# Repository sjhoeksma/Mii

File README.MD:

# Mii an Opensource Real Time, Timing solution
This solution can be used to create your own real time timing solution. It can be for example be used for mesuaring
the time needed to run a 10 meter sprint or do ski run.

We provide the hardware components, created with Eagle from CadSoft, emmbedded software written in arduino and a HTML5 app for Web & Mobile devices written with IONIC framework 1.3. For hardware components we provide the 3D models allowing you to print them your self.

## Components
1. MiiChrono and a MiiBeam make a start of finish line
2. MiiScoreboard can be used to show the time
3. MiiApp is the HMTL5 app
4. Mii3D are the 3D models for your printer in using openScad
5. Lib contains all libaries you need

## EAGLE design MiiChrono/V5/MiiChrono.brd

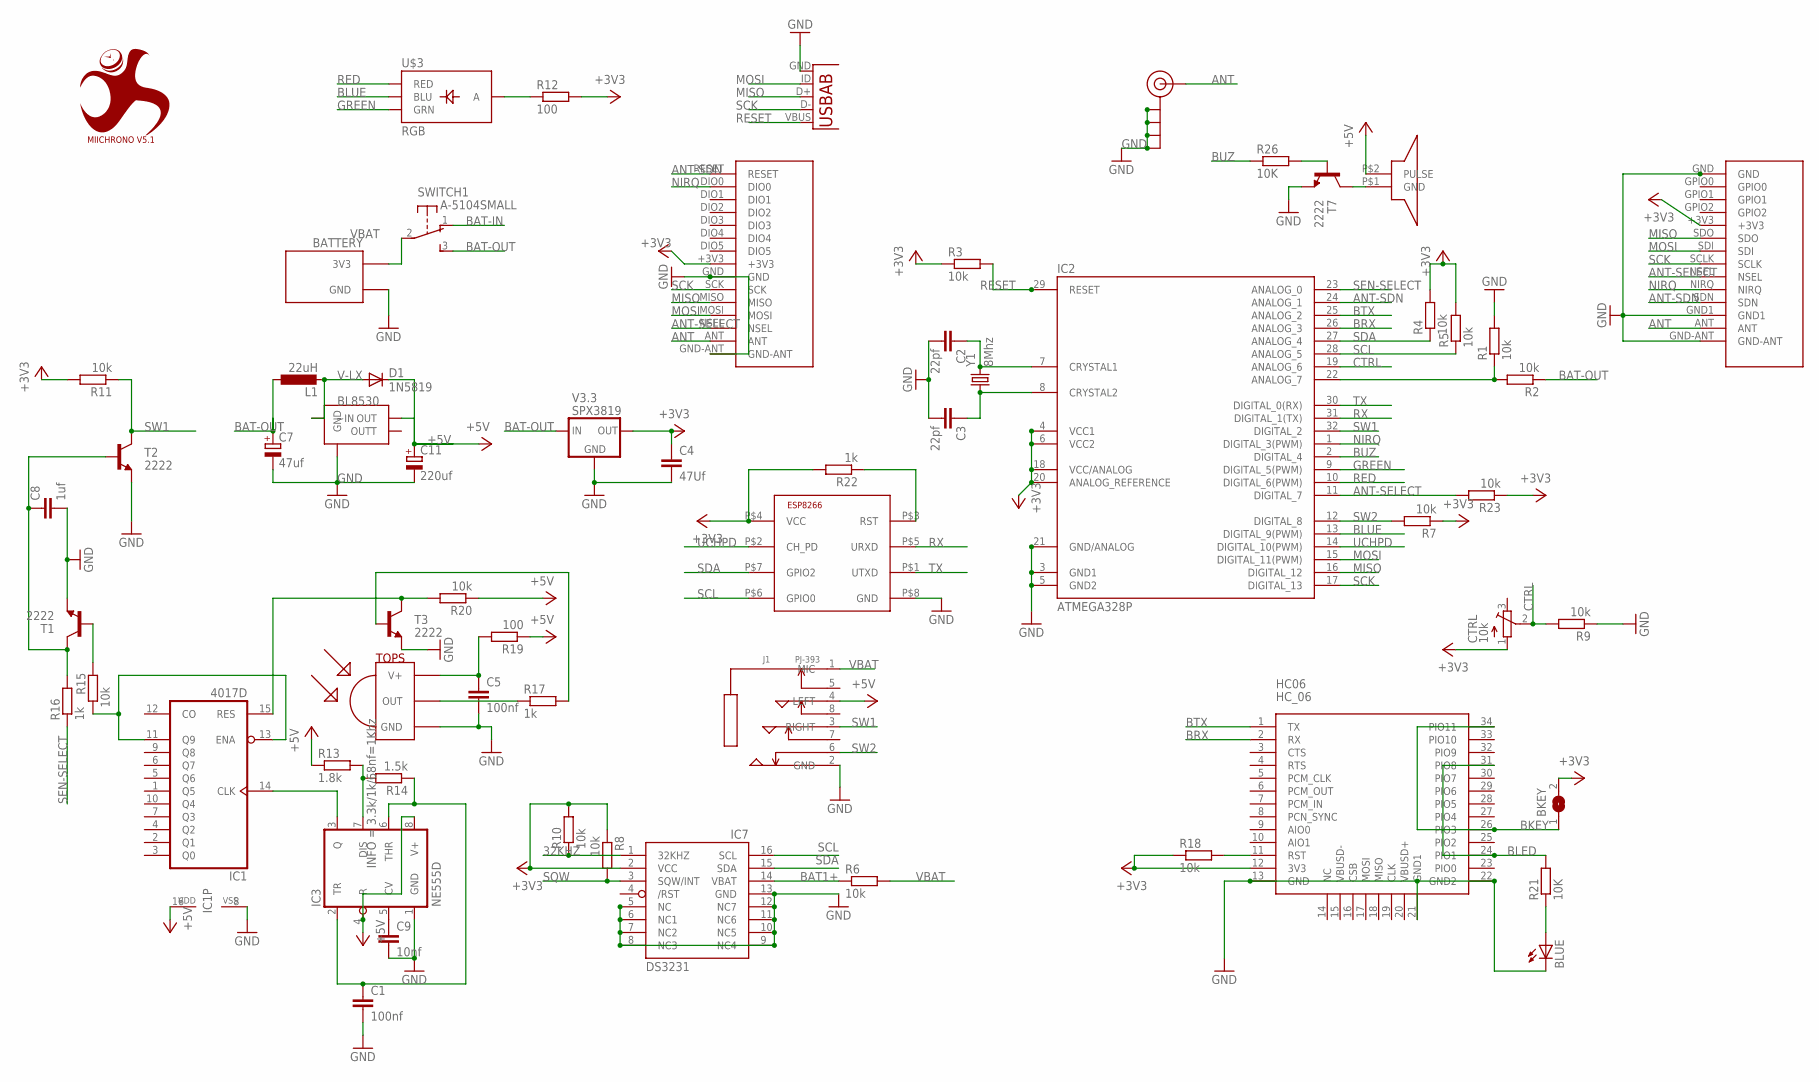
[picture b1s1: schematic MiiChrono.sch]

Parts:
BATTERY: GOPRO3BATTERY
BKEY: SOLDERJUMPER; SOLDERJUMPER_ARROW_NOPASTE
BL8530: BL8530; SOT89
BLUE: LEDCHIP-LED0805; CHIP-LED0805
BUZZER: BUZZER
C1, C5: 100nf; C0805
C2, C3: 22pf; C0805
C4: 47Uf; C0805
C7: 47uf; SMC_A
C8: 1uf; C0805
C9: 10nf; C0805
C11: 220uf; CT3528
CTRL: 10k; TC33X
D1: 1N5819; DO214AC
HC06: HC_06; BLUETOOTH_SMD
IC1: 4017D; SO16
IC2: ATMEGA328P; TQFP32-08
IC3: NE555D; SO08
IC7: DS3231/SO; SO16W
ISP1: USB-ABUSB_SIERK; USB_AB_MICRO_SJH
J1: PJ-393; AUDIO8P-SMD-3.5-14.5X6.1X4.0MM
J$1: SMA_EDGE; SMA-EDGE
L1: 22uH; L1812
R1, R2, R3, R4, R5, R6, R7, R8, R9, R10, R11, R15, R18, R20, R23: 10k; R0805
R12, R19: 100; R0805
R13: 1.8k; R0805
R14: 1.5k; R0805
R16, R17, R22: 1k; R0805
R21, R26: 10K; R0805
SWITCH: A-5104SMALL; A-5104-SMALL
T1, T2, T3, T7: 2222; SOT23
TOPS: TSOP4838; TSOP18XX
U$1: MIICHRONO V5.1; MIICHRONO
U$2: DRF1278F
U$3: RGB; LED-TRICOLOR-SMD
U$4: ESP8266-01; ESP-01
U$7: SI4432
V3.3: SPX3819; SOT23-5
Y1: 8Mhz; HC49UP

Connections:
32KHZ: IC7.1 (32KHZ), R10.1
+3V3: BKEY.2, C4.1, CTRL.1 (A), HC06.12 (3V3), IC2.4 (VCC1), IC2.6 (VCC2), IC2.18 (VCC/ANALOG), IC2.20 (ANALOG_REFERENCE), IC7.2 (VCC), R3.1, R4.2, R5.2, R7.1, R8.1, R10.2, R11.2, R12.2, R18.1, R22.2, R23.1, U$2.+3V3, U$4.P$4 (VCC), U$7.+3V3, V3.3.5 (OUT)
+5V: BL8530.2 (OUT), BUZZER.P$2 (PULSE), C11.+, D1.C, IC1.16 (VDD), IC3.4 (R), IC3.8 (V+), J1.4 (LEFT), R13.1, R19.1, R20.1
ANT: J$1.$P1 (SIGNAL), U$2.ANT, U$7.ANT
ANT-SDN: IC2.24 (ANALOG_1), U$2.RESET, U$7.SDN
ANT-SELECT: IC2.11 (DIGITAL_7), R23.2, U$2.NSEL, U$7.NSEL
BAT1+: IC7.14 (VBAT), R6.1
BAT-IN: SWITCH.1 (O)
BAT-OUT: C7.+, L1.1, R2.1, SWITCH.3 (S), V3.3.1 (IN), V3.3.3 (IN)
BKEY: BKEY.1, HC06.26 (PIO3), HC06.34 (PIO11)
BLED: HC06.24 (PIO1), HC06.31 (PIO8), R21.2
BLUE: IC2.13 (DIGITAL_9(PWM)), U$3.B (BLU)
BRX: HC06.2 (RX), IC2.26 (ANALOG_3)
BTX: HC06.1 (TX), IC2.25 (ANALOG_2)
BUZ: IC2.2 (DIGITAL_4), R26.1
CTRL: CTRL.2 (S), IC2.19 (ANALOG_6), R9.2
GND: BATTERY.GND, BL8530.1 (GND), BLUE.C, C1.2, C2.2, C3.2, C4.2, C5.2, C7.-, C8.2, C9.2, C11.-, HC06.13 (GND), HC06.21 (GND1), HC06.22 (GND2), IC1.8 (VSS), IC2.3 (GND1), IC2.5 (GND2), IC2.21 (GND/ANALOG), IC3.1 (GND), IC7.5 (NC), IC7.6 (NC1), IC7.7 (NC2), IC7.8 (NC3), IC7.9 (NC4), IC7.10 (NC5), IC7.11 (NC6), IC7.12 (NC7), IC7.13 (GND), ISP1.GND, J1.2 (GND), J$1.GND@0 (GND), J$1.GND@1 (GND), J$1.GND@2 (GND), J$1.GND@3 (GND), R1.2, R9.1, T1.2 (E), T2.2 (E), T3.2 (E), T7.2 (E), TOPS.GND, U$2.GND, U$2.GND-ANT, U$4.P$8 (GND), U$7.GND, U$7.GND1, U$7.GND-ANT, V3.3.2 (GND)
GREEN: IC2.9 (DIGITAL_5(PWM)), U$3.G (GRN)
MISO: IC2.16 (DIGITAL_12), ISP1.D+, U$2.MISO, U$7.SDO
MOSI: IC2.15 (DIGITAL_11(PWM)), ISP1.ID (USBID), U$2.MOSI, U$7.SDI
unnamed: R17.2, T3.1 (B)
unnamed: C9.1, IC3.5 (CV)
unnamed: HC06.11 (RST), R18.2
unnamed: C8.1, R16.2, T1.3 (C), T2.1 (B)
unnamed: IC1.11 (Q9), IC1.13 (ENA), R15.1
unnamed: R22.1, U$4.P$3 (RST)
unnamed: C3.1, IC2.8 (CRYSTAL2), Y1.1
unnamed: C2.1, IC2.7 (CRYSTAL1), Y1.2
unnamed: R15.2, T1.1 (B)
unnamed: R12.1, U$3.A
unnamed: C1.1, IC3.2 (TR), IC3.6 (THR), R14.1
unnamed: BLUE.A, R21.1
unnamed: IC1.14 (CLK), IC3.3 (Q)
unnamed: IC3.7 (DIS), R13.2, R14.2
unnamed: R17.1, TOPS.OUT
unnamed: C5.1, R19.2, TOPS.VCC (V+)
unnamed: IC1.15 (RES), R20.2, T3.3 (C)
unnamed: IC2.22 (ANALOG_7), R1.1, R2.2
unnamed: R26.2, T7.1 (B)
unnamed: BUZZER.P$1 (GND), T7.3 (C)
NIRQ: IC2.1 (DIGITAL_3(PWM)), U$2.DIO0, U$7.NIRQ
RED: IC2.10 (DIGITAL_6(PWM)), U$3.R (RED)
RESET: IC2.29 (RESET), ISP1.VBUS, R3.2
RX: IC2.31 (DIGITAL_1(TX)), U$4.P$5 (URXD)
SCK: IC2.17 (DIGITAL_13), ISP1.D-, U$2.SCK, U$7.SCLK
SCL: IC2.28 (ANALOG_5), IC7.16 (SCL), R5.1, U$4.P$6 (GPIO0)
SDA: IC2.27 (ANALOG_4), IC7.15 (SDA), R4.1, U$4.P$7 (GPIO2)
SEN-SELECT: IC2.23 (ANALOG_0), R16.1
SQW: IC7.3 (SQW/INT), R8.2
SW1: IC2.32 (DIGITAL_2), J1.3 (RIGHT), R11.1, T2.3 (C)
SW2: IC2.12 (DIGITAL_8), J1.6, R7.2
TX: IC2.30 (DIGITAL_0(RX)), U$4.P$1 (UTXD)
UCHPD: IC2.14 (DIGITAL_10(PWM)), U$4.P$2 (CH_PD)
V-LX: BL8530.3 (~IN), D1.A, L1.2
VBAT: BATTERY.3V3, J1.1 (MIC), R6.2, SWITCH.2

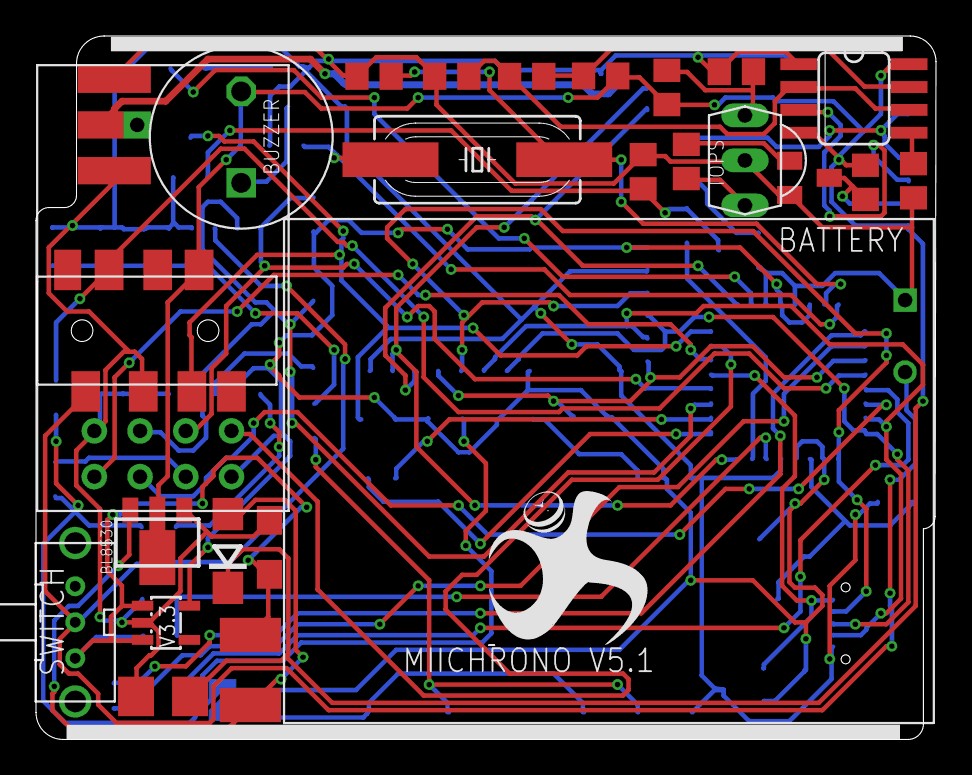
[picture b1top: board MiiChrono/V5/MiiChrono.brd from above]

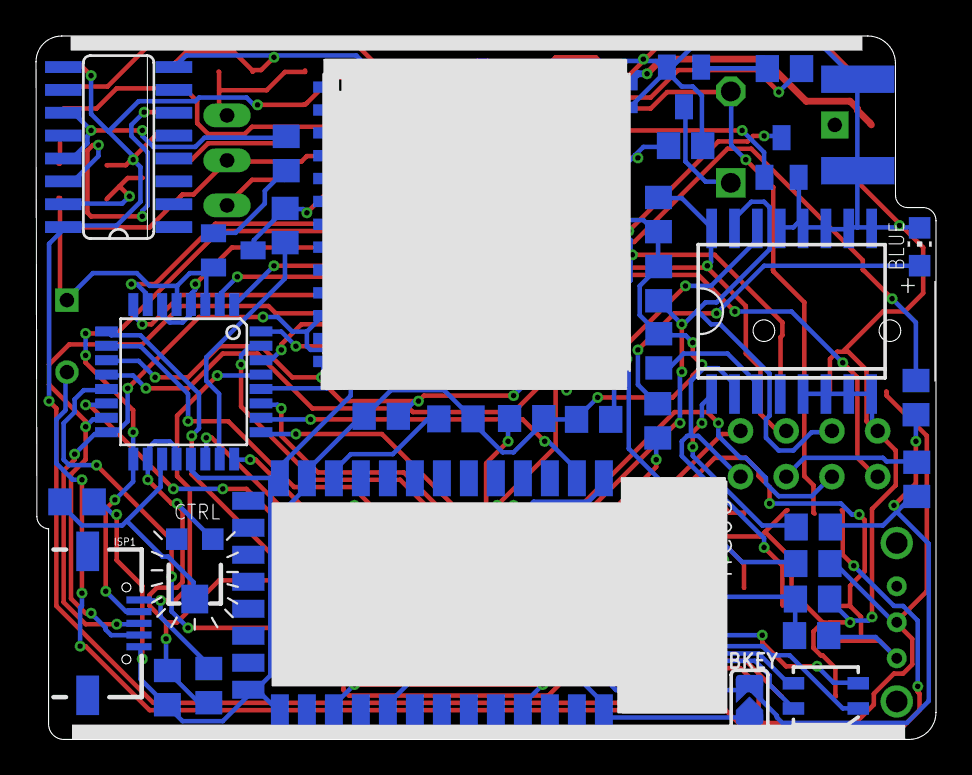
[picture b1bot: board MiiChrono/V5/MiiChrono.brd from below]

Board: 2 copper layers, 50.0 x 39.1 mm, 62 parts (35 on the bottom side), 54 nets.

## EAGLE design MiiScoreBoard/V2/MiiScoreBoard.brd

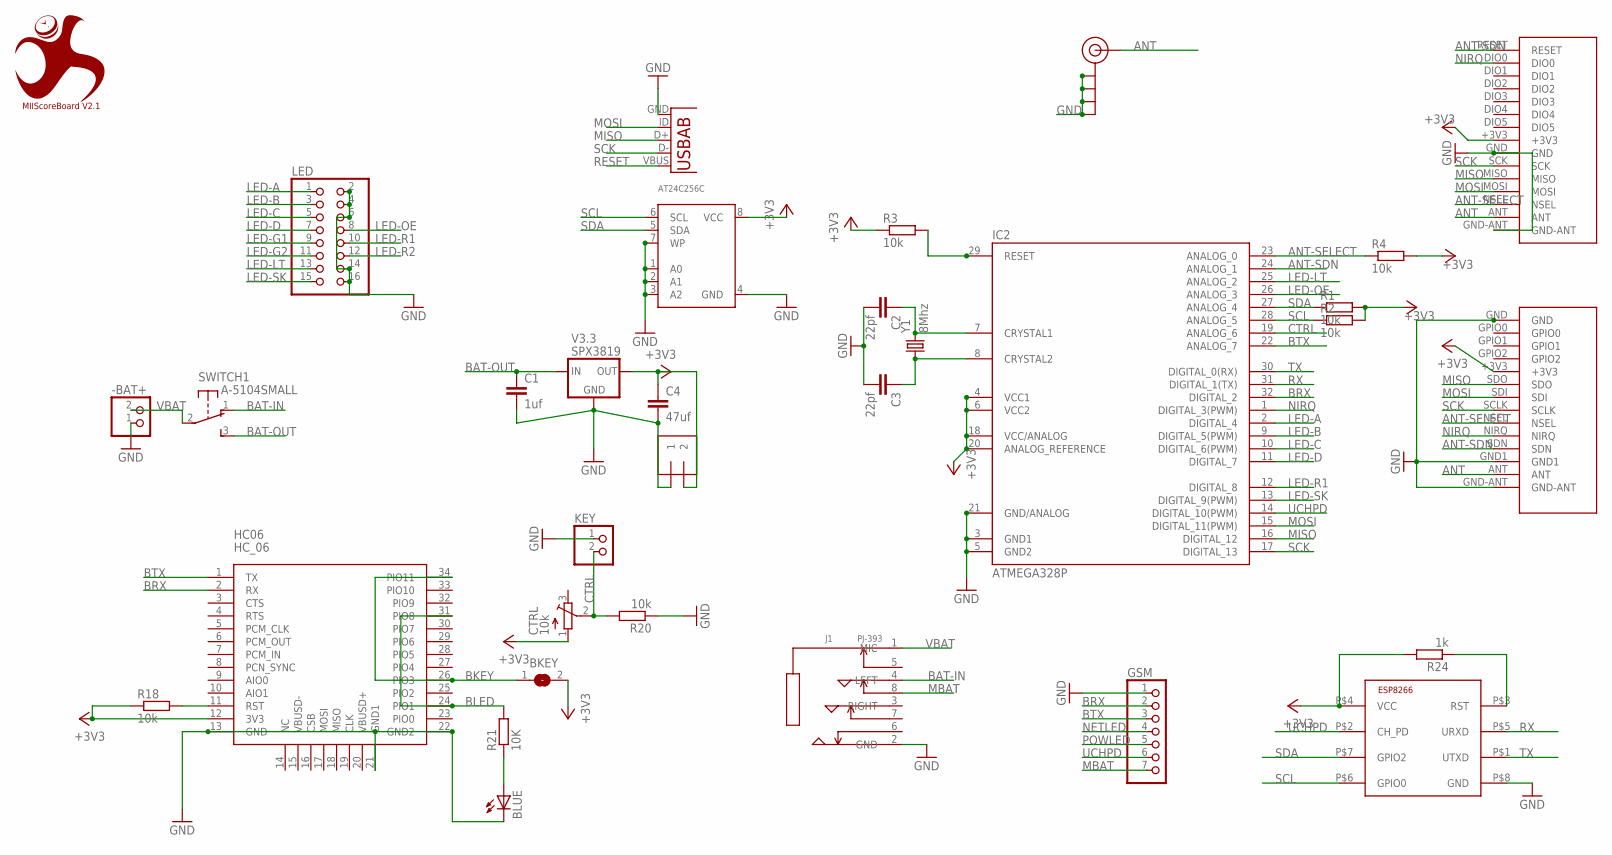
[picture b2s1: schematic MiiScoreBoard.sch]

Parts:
-BAT+: JST_2PIN-THM; JST-PH-2-THM
-LED+: -BAT+; 1X2-3.5MM
AT24C256C: EEPROM_I2C_SOIC8_GENERIC; SOIC8_150MIL
BKEY: SOLDERJUMPER; SOLDERJUMPER_ARROW_NOPASTE
BLUE: LEDCHIP-LED0805; CHIP-LED0805
C1: 1uf; C0805
C2, C3: 22pf; C0805
C4: 47uf; C0805
CTRL: 10k; TC33X
GSM: PINHD-1X07_2.54; 1X07
HC06: HC_06; BLUETOOTH_SMD
IC2: ATMEGA328P; TQFP32-08
ISP1: USB-ABUSB_SIERK; USB_AB_MICRO_SJH
J1: PJ-393; AUDIO8P-SMD-3.5-14.5X6.1X4.0MM
J$1: SMA_EDGE; SMA-EDGE
KEY: PINHD-1X02_2.54-90°; 1X02/90
LED: PINHD-2X08_2.54; 2X08
R1, R2, R3, R4, R18, R20: 10k; R0805
R21: 10K; R0805
R24: 1k; R0805
SWITCH: A-5104SMALL; A-5104-SMALL
U$1: MIIScoreBoard V2.1; MIICHRONO
U$2: DRF1278F
U$6: ESP8266-01; ESP-01
U$7: SI4432
V3.3: SPX3819; SOT23-5
Y1: 8Mhz; HC49UP

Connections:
+3V3: -LED+.2, AT24C256C.8 (VCC), BKEY.2, C4.1, CTRL.1 (A), HC06.12 (3V3), IC2.4 (VCC1), IC2.6 (VCC2), IC2.18 (VCC/ANALOG), IC2.20 (ANALOG_REFERENCE), R1.2, R2.2, R3.1, R4.2, R18.1, R24.2, U$2.+3V3, U$6.P$4 (VCC), U$7.+3V3, V3.3.5 (OUT)
ANT: J$1.$P1 (SIGNAL), U$2.ANT, U$7.ANT
ANT-SDN: IC2.24 (ANALOG_1), U$2.RESET, U$7.SDN
ANT-SELECT: IC2.23 (ANALOG_0), R4.1, U$2.NSEL, U$7.NSEL
BAT-IN: J1.4 (LEFT), SWITCH.1 (O)
BAT-OUT: C1.1, SWITCH.3 (S), V3.3.1 (IN), V3.3.3 (IN)
BKEY: BKEY.1, HC06.26 (PIO3), HC06.34 (PIO11)
BLED: HC06.24 (PIO1), HC06.31 (PIO8), R21.2
BRX: GSM.2, HC06.2 (RX), IC2.32 (DIGITAL_2)
BTX: GSM.3, HC06.1 (TX), IC2.22 (ANALOG_7)
CTRL: CTRL.2 (S), IC2.19 (ANALOG_6), KEY.2, R20.2
GND: -BAT+.1 (2), -LED+.1, AT24C256C.1 (A0), AT24C256C.2 (A1), AT24C256C.3 (A2), AT24C256C.4 (GND), AT24C256C.7 (WP), BLUE.C, C1.2, C2.2, C3.2, C4.2, GSM.1, HC06.13 (GND), HC06.21 (GND1), HC06.22 (GND2), IC2.3 (GND1), IC2.5 (GND2), IC2.21 (GND/ANALOG), ISP1.GND, J1.2 (GND), J$1.GND@0 (GND), J$1.GND@1 (GND), J$1.GND@2 (GND), J$1.GND@3 (GND), KEY.1, LED.2, LED.4, LED.6, LED.14, LED.16, R20.1, U$2.GND, U$2.GND-ANT, U$6.P$8 (GND), U$7.GND, U$7.GND1, U$7.GND-ANT, V3.3.2 (GND)
LED-A: IC2.2 (DIGITAL_4), LED.1
LED-B: IC2.9 (DIGITAL_5(PWM)), LED.3
LED-C: IC2.10 (DIGITAL_6(PWM)), LED.5
LED-D: IC2.11 (DIGITAL_7), LED.7
LED-G1: LED.9
LED-G2: LED.11
LED-LT: IC2.25 (ANALOG_2), LED.13
LED-OE: IC2.26 (ANALOG_3), LED.8
LED-R1: IC2.12 (DIGITAL_8), LED.10
LED-R2: LED.12
LED-SK: IC2.13 (DIGITAL_9(PWM)), LED.15
MBAT: GSM.7, J1.8
MISO: IC2.16 (DIGITAL_12), ISP1.D+, U$2.MISO, U$7.SDO
MOSI: IC2.15 (DIGITAL_11(PWM)), ISP1.ID (USBID), U$2.MOSI, U$7.SDI
unnamed: HC06.11 (RST), R18.2
unnamed: C3.1, IC2.8 (CRYSTAL2), Y1.1
unnamed: C2.1, IC2.7 (CRYSTAL1), Y1.2
unnamed: R24.1, U$6.P$3 (RST)
unnamed: BLUE.A, R21.1
NETLED: GSM.4
NIRQ: IC2.1 (DIGITAL_3(PWM)), U$2.DIO0, U$7.NIRQ
POWLED: GSM.5
RESET: IC2.29 (RESET), ISP1.VBUS, R3.2
RX: IC2.31 (DIGITAL_1(TX)), U$6.P$5 (URXD)
SCK: IC2.17 (DIGITAL_13), ISP1.D-, U$2.SCK, U$7.SCLK
SCL: AT24C256C.6 (SCL), IC2.28 (ANALOG_5), R2.1, U$6.P$6 (GPIO0)
SDA: AT24C256C.5 (SDA), IC2.27 (ANALOG_4), R1.1, U$6.P$7 (GPIO2)
TX: IC2.30 (DIGITAL_0(RX)), U$6.P$1 (UTXD)
UCHPD: GSM.6, IC2.14 (DIGITAL_10(PWM)), U$6.P$2 (CH_PD)
VBAT: -BAT+.2 (1), J1.1 (MIC), SWITCH.2

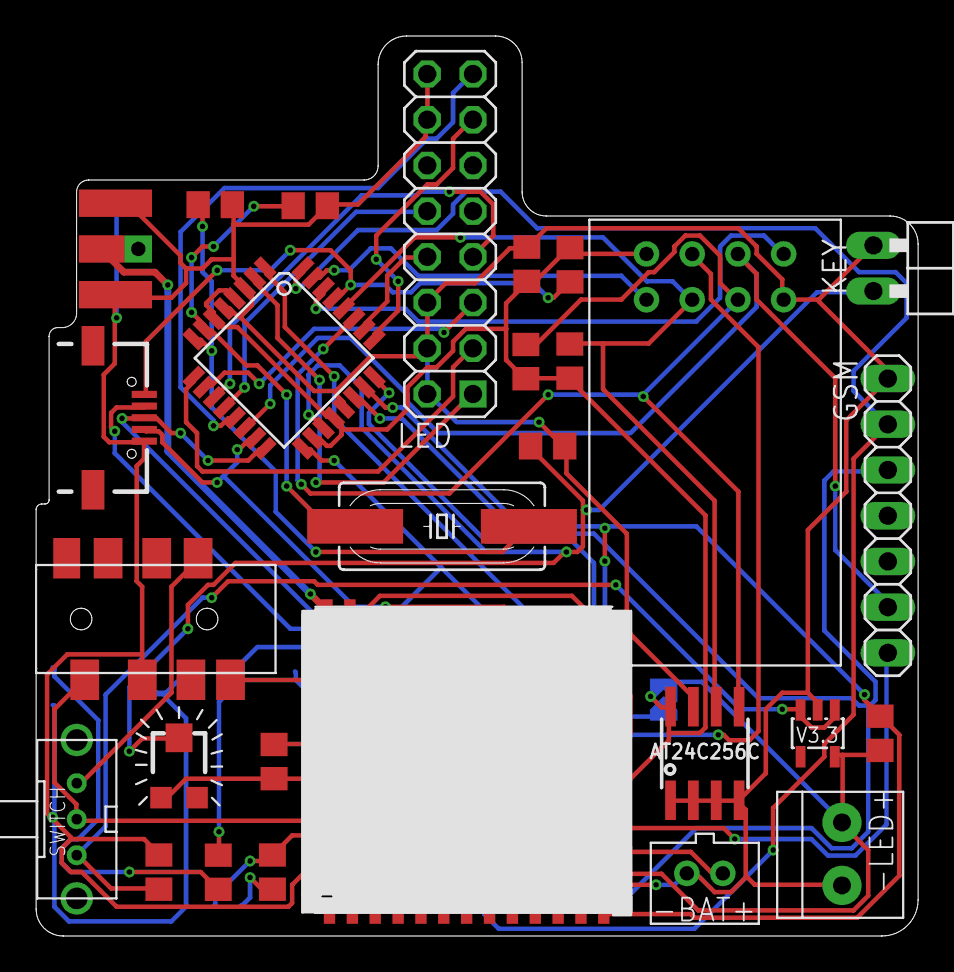
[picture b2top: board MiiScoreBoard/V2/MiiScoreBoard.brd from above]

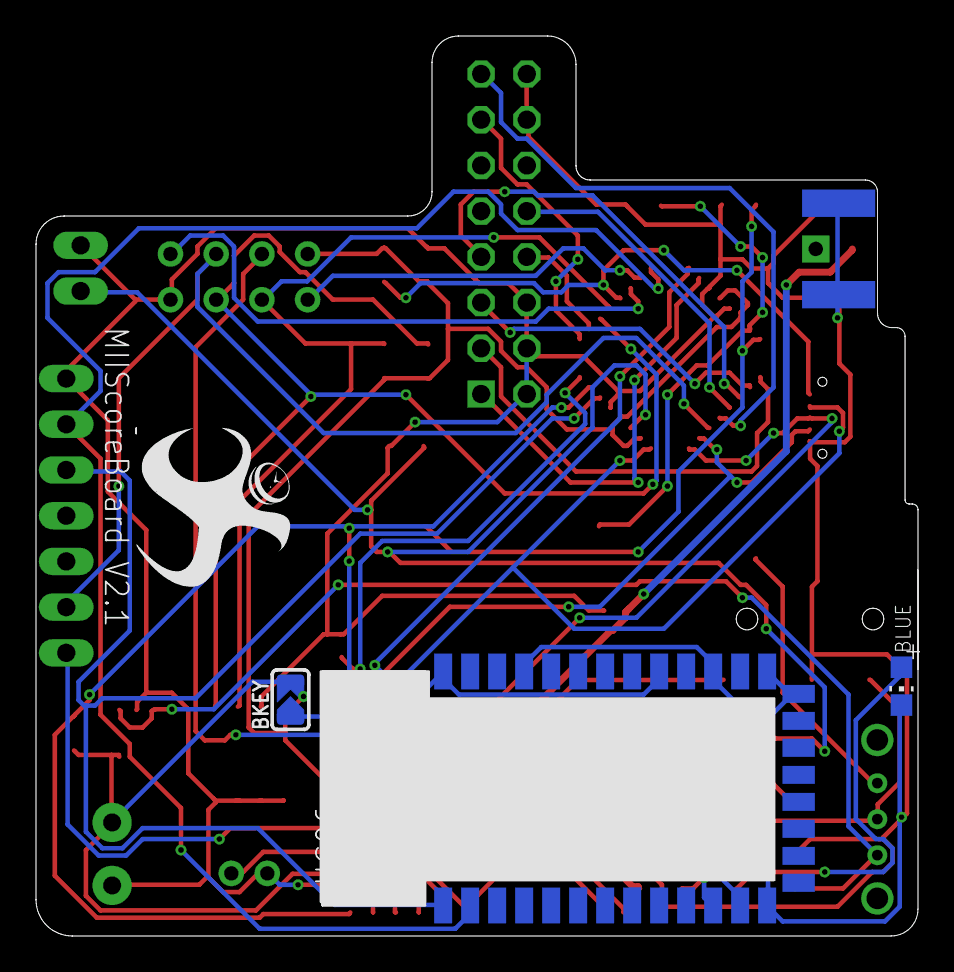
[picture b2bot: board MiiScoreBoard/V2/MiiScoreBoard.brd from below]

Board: 2 copper layers, 49.0 x 50.0 mm, 33 parts (4 on the bottom side), 37 nets.

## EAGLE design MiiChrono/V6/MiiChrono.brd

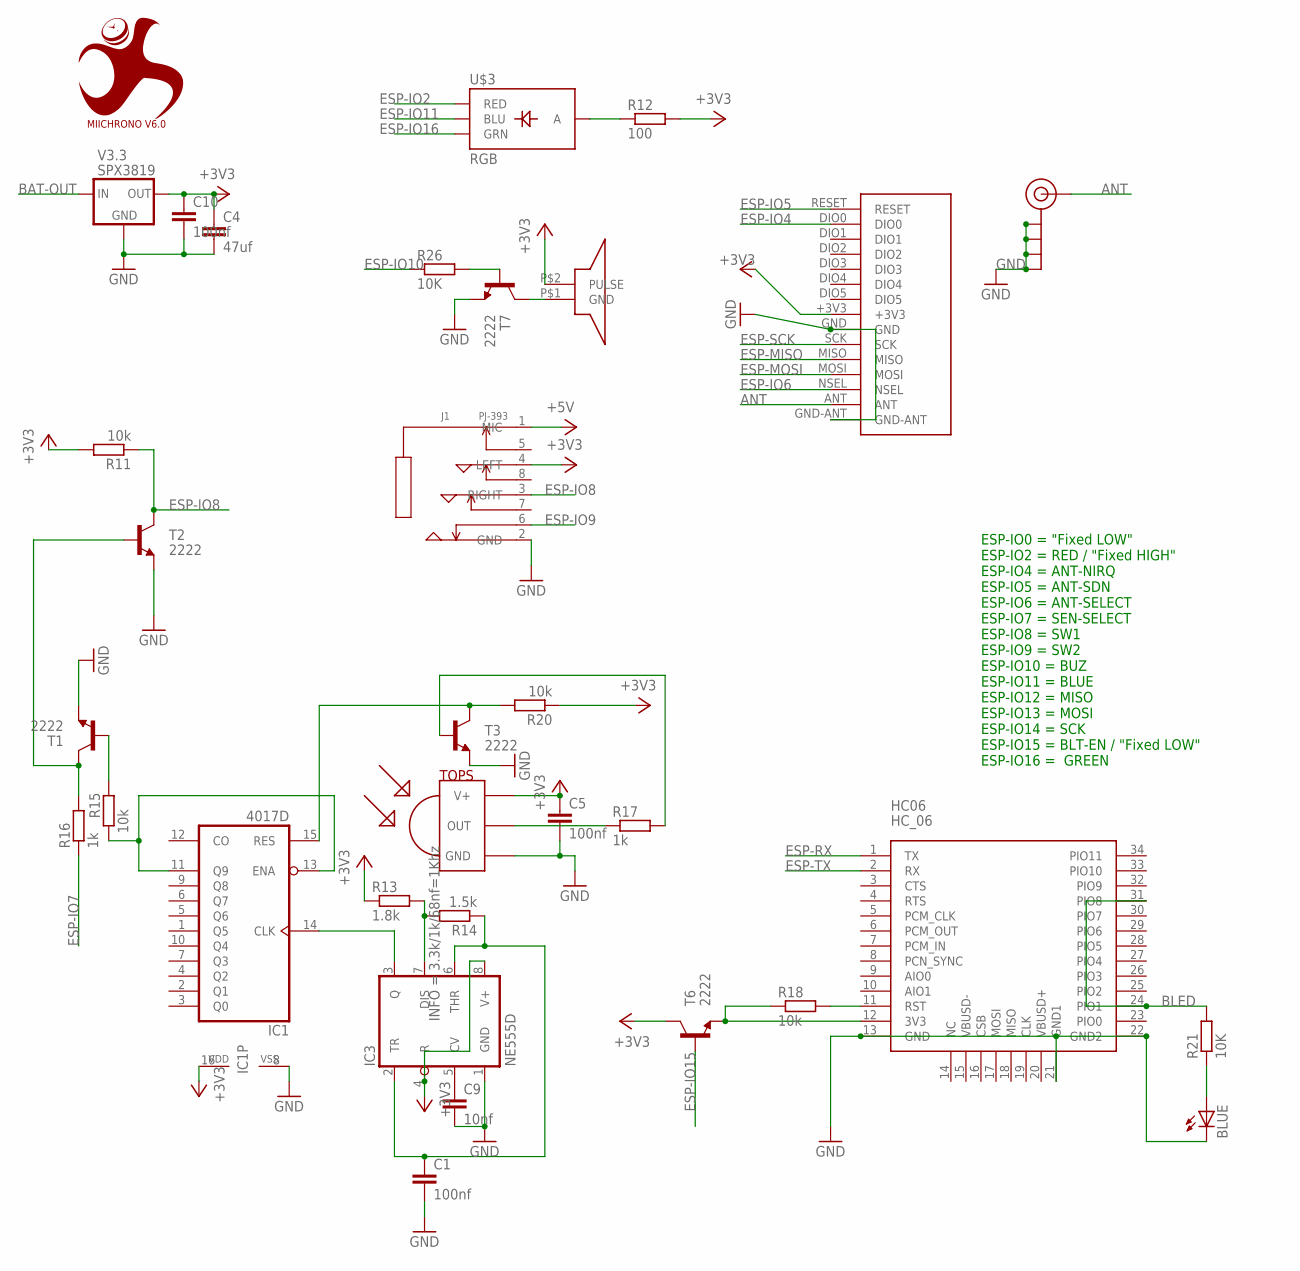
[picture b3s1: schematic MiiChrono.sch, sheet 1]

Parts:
BLUE: LEDCHIP-LED0805; CHIP-LED0805
BUZZER: BUZZER
C1, C5, C10: 100nf; C0805
C4: 47uf; C0805
C9: 10nf; C0805
HC06: HC_06; BLUETOOTH_SMD
IC1: 4017D; SO16
IC3: NE555D; SO08
J1: PJ-393; AUDIO8P-SMD-3.5-14.5X6.1X4.0MM
J$1: SMA_EDGE; SMA-EDGE
R11, R15, R18, R20: 10k; R0805
R12: 100; R0805
R13: 1.8k; R0805
R14: 1.5k; R0805
R16, R17: 1k; R0805
R21, R26: 10K; R0805
T1, T2, T3, T6, T7: 2222; SOT23
TOPS: TSOP4838; TSOP18XX
U$1: MIICHRONO V6.0; MIICHRONO
U$2: DRF1278F
U$3: RGB; LED-TRICOLOR-SMD
V3.3: SPX3819; SOT23-5

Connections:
+3V3: BUZZER.P$2 (PULSE), C4.1, C5.1, C10.1, IC1.16 (VDD), IC3.4 (R), IC3.8 (V+), J1.4 (LEFT), R11.2, R12.2, R13.1, R20.1, T6.3 (C), TOPS.VCC (V+), U$2.+3V3, V3.3.5 (OUT)
+5V: J1.1 (MIC); also elsewhere on the board
ANT: J$1.$P1 (SIGNAL), U$2.ANT
BAT-OUT: V3.3.1 (IN), V3.3.3 (IN); also elsewhere on the board
BLED: HC06.24 (PIO1), HC06.31 (PIO8), R21.2
ESP-IO2: U$3.R (RED); also elsewhere on the board
ESP-IO4: U$2.DIO0; also elsewhere on the board
ESP-IO5: U$2.RESET; also elsewhere on the board
ESP-IO6: U$2.NSEL; also elsewhere on the board
ESP-IO7: R16.1; also elsewhere on the board
ESP-IO8: J1.3 (RIGHT), R11.1, T2.3 (C); also elsewhere on the board
ESP-IO9: J1.6; also elsewhere on the board
ESP-IO10: R26.1; also elsewhere on the board
ESP-IO11: U$3.B (BLU); also elsewhere on the board
ESP-IO15: T6.1 (B); also elsewhere on the board
ESP-IO16: U$3.G (GRN); also elsewhere on the board
ESP-MISO: U$2.MISO; also elsewhere on the board
ESP-MOSI: U$2.MOSI; also elsewhere on the board
ESP-RX: HC06.1 (TX); also elsewhere on the board
ESP-SCK: U$2.SCK; also elsewhere on the board
ESP-TX: HC06.2 (RX); also elsewhere on the board
GND: BLUE.C, C1.2, C4.2, C5.2, C9.2, C10.2, HC06.13 (GND), HC06.21 (GND1), HC06.22 (GND2), IC1.8 (VSS), IC3.1 (GND), J1.2 (GND), J$1.GND@0 (GND), J$1.GND@1 (GND), J$1.GND@2 (GND), J$1.GND@3 (GND), T1.2 (E), T2.2 (E), T3.2 (E), T7.2 (E), TOPS.GND, U$2.GND, U$2.GND-ANT, V3.3.2 (GND); also elsewhere on the board
unnamed: R17.2, T3.1 (B)
unnamed: C9.1, IC3.5 (CV)
unnamed: R16.2, T1.3 (C), T2.1 (B)
unnamed: IC1.11 (Q9), IC1.13 (ENA), R15.1
unnamed: HC06.12 (3V3), R18.1, T6.2 (E)
unnamed: R15.2, T1.1 (B)
unnamed: R12.1, U$3.A
unnamed: C1.1, IC3.2 (TR), IC3.6 (THR), R14.1
unnamed: HC06.11 (RST), R18.2
unnamed: IC1.14 (CLK), IC3.3 (Q)
unnamed: IC3.7 (DIS), R13.2, R14.2
unnamed: R17.1, TOPS.OUT
unnamed: BLUE.A, R21.1
unnamed: IC1.15 (RES), R20.2, T3.3 (C)
unnamed: R26.2, T7.1 (B)
unnamed: BUZZER.P$1 (GND), T7.3 (C)

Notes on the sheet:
ESP-IO0 = "Fixed LOW" ESP-IO2 = RED / "Fixed HIGH" ESP-IO4 = ANT-NIRQ ESP-IO5 = ANT-SDN ESP-IO6 = ANT-SELECT ESP-IO7 = SEN-SELECT ESP-IO8 = SW1 ESP-IO9 = SW2 ESP-IO10 = BUZ ESP-IO11 = BLUE ESP-IO12 = MISO ESP-IO13 = MOSI ESP-IO14 = SCK ESP-IO15 = BLT-EN / "Fixed LOW" ESP-IO16 = GREEN

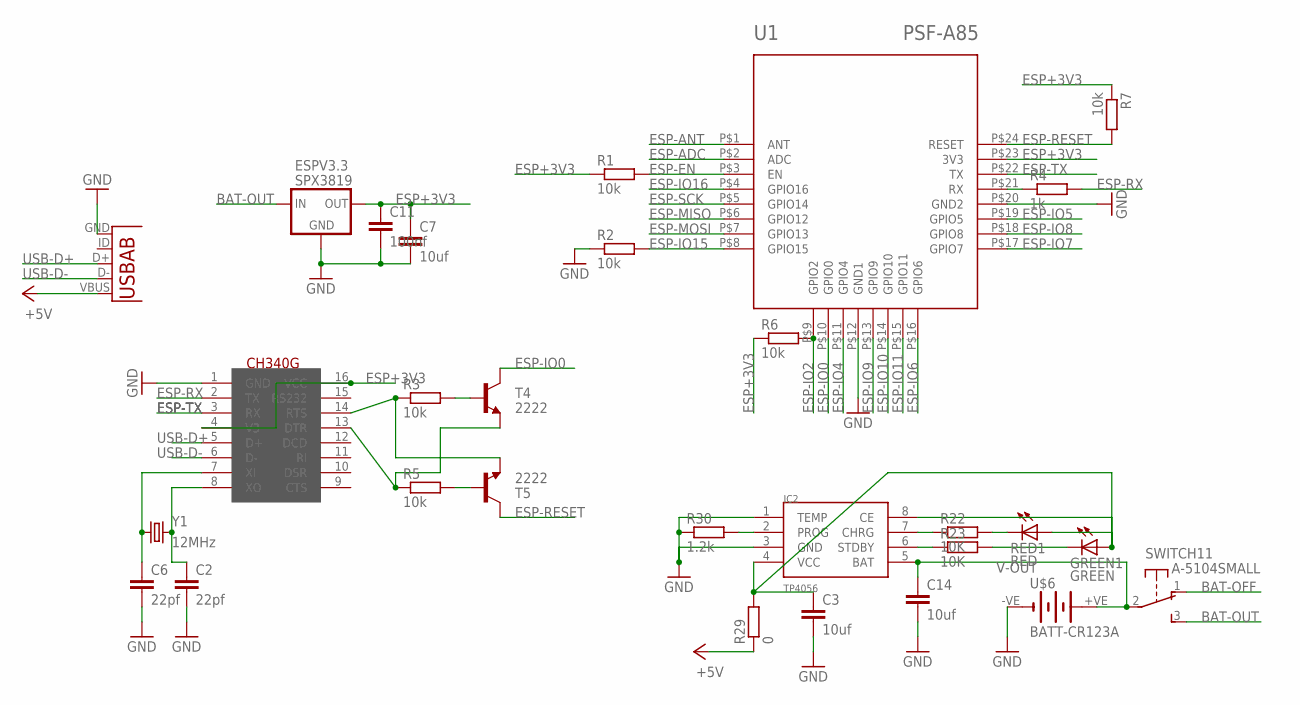
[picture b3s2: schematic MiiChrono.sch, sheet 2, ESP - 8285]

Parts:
C2, C6: 22pf; C0805
C3, C7, C14: 10uf; C0805
C11: 100nf; C0805
ESPV3.3: SPX3819; SOT23-5
GREEN1: GREEN; CHIP-LED0805
IC2: TP4056; SOP-8
ISP2: USB-ABUSB_SIERK; USB_AB_MICRO_SJH
R1, R2, R3, R5, R6, R7: 10k; R0805
R4: 1k; R0805
R22, R23: 10K; R0805
R29: 0; R0805
R30: 1.2k; R0805
RED1: RED; CHIP-LED0805
SWITCH1: A-5104SMALL; A-5104-SMALL
T4, T5: 2222; SOT23
U1: PSF-A85
U$5: CH340G; SOIC16
U$6: BATT-CR123A; KEYSTONE-2/3A
Y1: 12MHz; CRYSTAL-SMD-5X3

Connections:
+5V: ISP2.VBUS, R29.1; also elsewhere on the board
BAT-OFF: SWITCH1.1 (O)
BAT-OUT: ESPV3.3.1 (IN), ESPV3.3.3 (IN), SWITCH1.3 (S); also elsewhere on the board
ESP+3V3: C7.1, C11.1, ESPV3.3.5 (OUT), R1.1, R6.1, R7.1, U1.P$23 (3V3), U$5.4 (V3), U$5.16 (VCC)
ESP-ADC: U1.P$2 (ADC)
ESP-ANT: U1.P$1 (ANT)
ESP-EN: R1.2, U1.P$3 (EN)
ESP-IO0: T4.3 (C), U1.P$10 (GPIO0)
ESP-IO2: R6.2, U1.P$9 (GPIO2); also elsewhere on the board
ESP-IO4: U1.P$11 (GPIO4); also elsewhere on the board
ESP-IO5: U1.P$19 (GPIO5); also elsewhere on the board
ESP-IO6: U1.P$16 (GPIO6); also elsewhere on the board
ESP-IO7: U1.P$17 (GPIO7); also elsewhere on the board
ESP-IO8: U1.P$18 (GPIO8); also elsewhere on the board
ESP-IO9: U1.P$13 (GPIO9); also elsewhere on the board
ESP-IO10: U1.P$14 (GPIO10); also elsewhere on the board
ESP-IO11: U1.P$15 (GPIO11); also elsewhere on the board
ESP-IO15: R2.2, U1.P$8 (GPIO15); also elsewhere on the board
ESP-IO16: U1.P$4 (GPIO16); also elsewhere on the board
ESP-MISO: U1.P$6 (GPIO12); also elsewhere on the board
ESP-MOSI: U1.P$7 (GPIO13); also elsewhere on the board
ESP-RESET: R7.2, T5.3 (C), U1.P$24 (RESET)
ESP-RX: R4.2, U$5.2 (TX); also elsewhere on the board
ESP-SCK: U1.P$5 (GPIO14); also elsewhere on the board
ESP-TX: U1.P$22 (TX), U$5.3 (RX); also elsewhere on the board
GND: C2.2, C3.2, C6.2, C7.2, C11.2, C14.2, ESPV3.3.2 (GND), IC2.1 (TEMP), IC2.3 (GND), ISP2.GND, R2.1, R30.1, U1.P$12 (GND1), U1.P$20 (GND2), U$5.1 (GND), U$6.-VE (-); also elsewhere on the board
unnamed: C6.1, U$5.7 (XI), Y1.1
unnamed: C2.1, U$5.8 (XO), Y1.3 (2)
unnamed: R3.1, T5.2 (E), U$5.14 (RTS)
unnamed: R5.1, T4.2 (E), U$5.13 (DTR)
unnamed: R5.2, T5.1 (B)
unnamed: R3.2, T4.1 (B)
unnamed: R4.1, U1.P$21 (RX)
unnamed: GREEN1.C, R23.2
unnamed: R22.2, RED1.C
unnamed: IC2.7 (CHRG), R22.1
unnamed: IC2.6 (STDBY), R23.1
unnamed: IC2.2 (PROG), R30.2
USB-D+: ISP2.D+, U$5.5 (D+)
USB-D-: ISP2.D-, U$5.6 (D-)
V-IN: C3.1, GREEN1.A, IC2.4 (VCC), IC2.8 (CE), R29.2, RED1.A
V-OUT: C14.1, IC2.5 (BAT), SWITCH1.2, U$6.+VE (+)

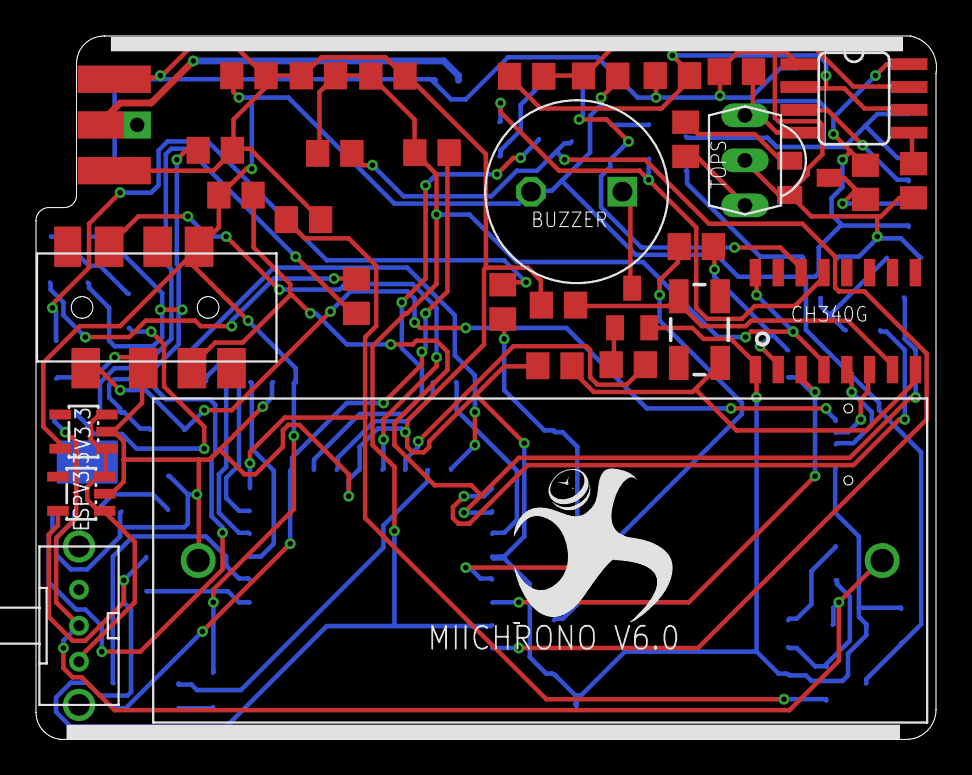
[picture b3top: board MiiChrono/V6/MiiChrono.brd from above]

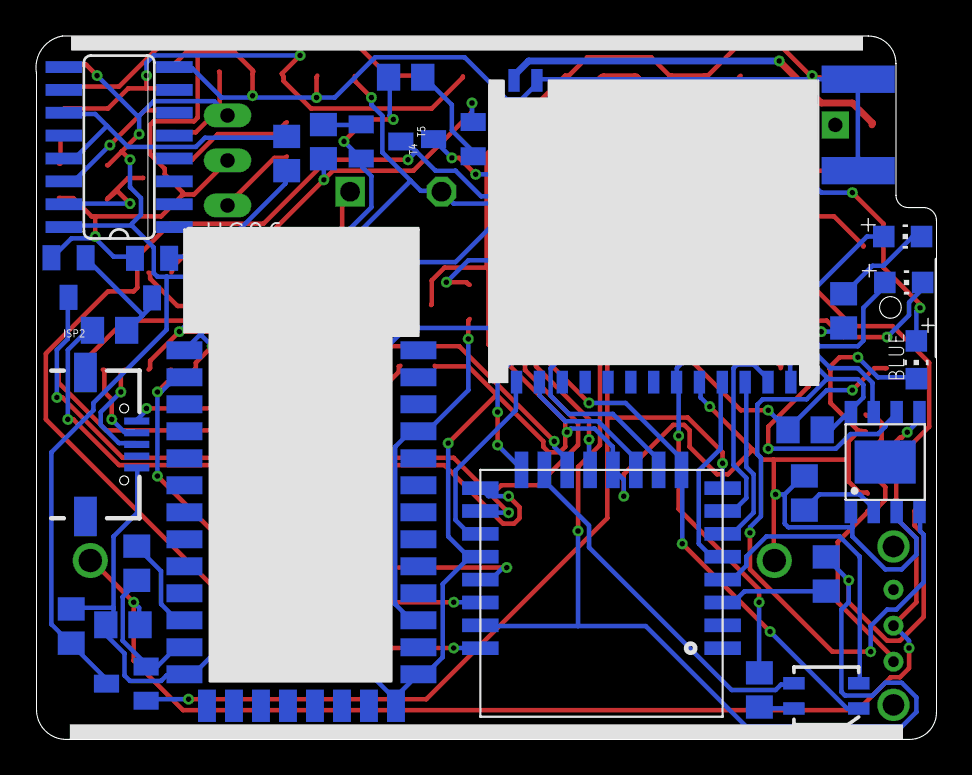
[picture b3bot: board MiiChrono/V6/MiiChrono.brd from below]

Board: 2 copper layers, 50.0 x 39.1 mm, 62 parts (27 on the bottom side), 58 nets.

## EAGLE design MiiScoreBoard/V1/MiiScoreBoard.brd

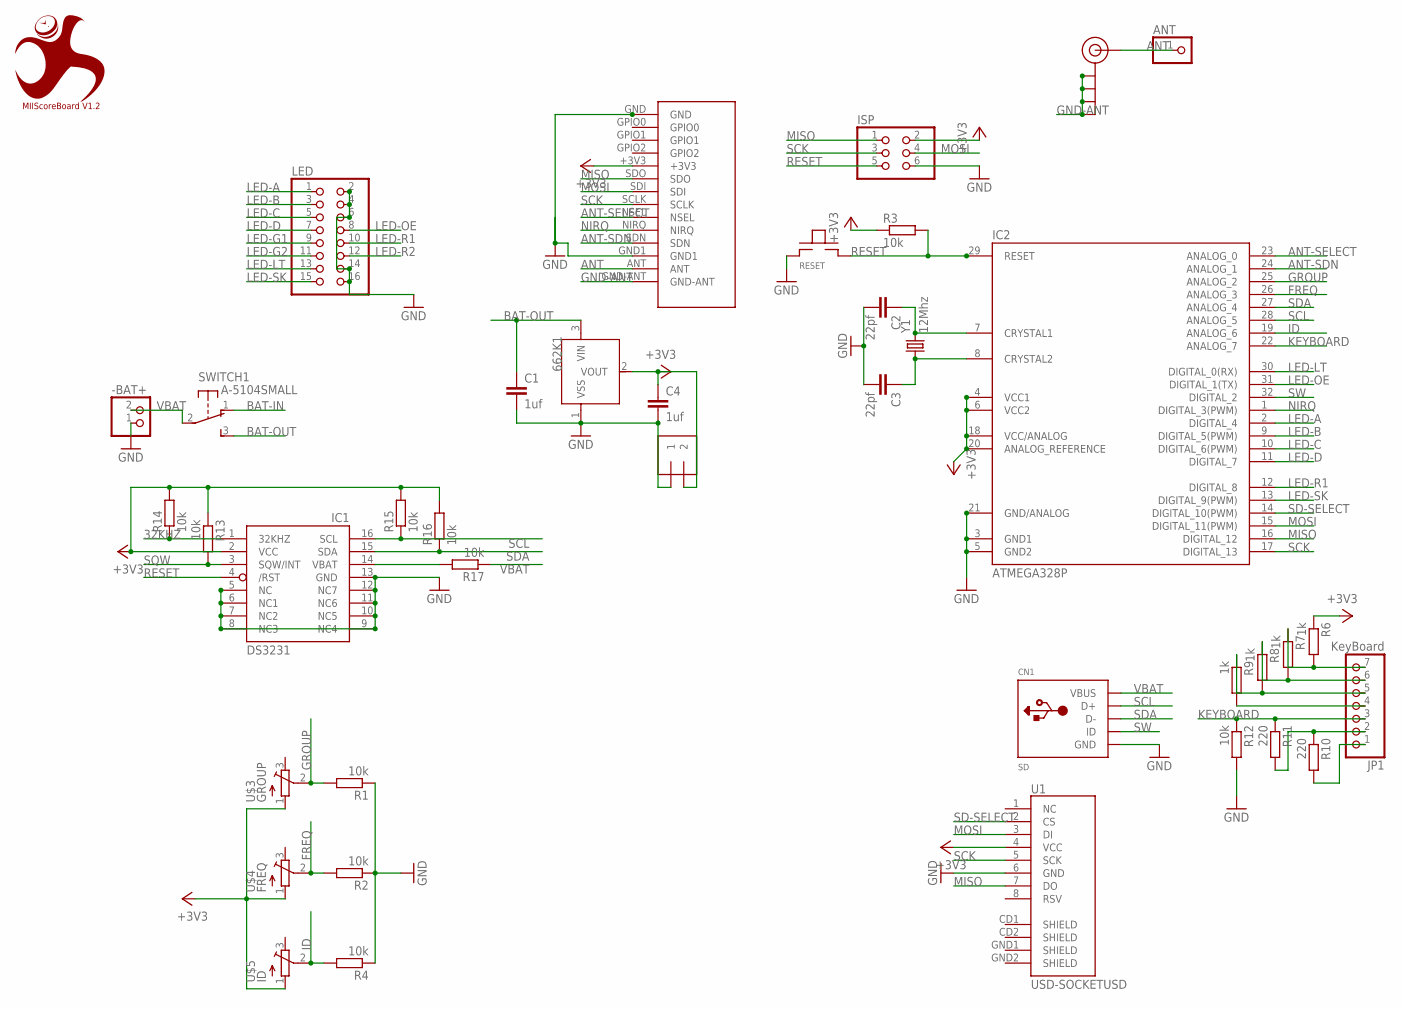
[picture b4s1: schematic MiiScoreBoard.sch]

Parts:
662K1: XC6206; SOT23
+LED-: -BAT+; 1X2-3.5MM
-BAT+: JST_2PIN-THM; JST-PH-2-THM
ANT: PINHD-1X01_2.00; 1X01M
C1, C4: 1uf; C0805
C2, C3: 22pf; C0805
CN1: SD; USB-MINIB
IC1: DS3231/SO; SO16W
IC2: ATMEGA328P; TQFP32-08
ISP: PINHD-2X03_2.00; 2X03M
J$1: SMA_EDGE; SMA-EDGE
JP1: KeyBoard; 1X07
LED: PINHD-2X08_2.54; 2X08
R1, R2, R3, R4, R12, R13, R14, R15, R16, R17: 10k; R0805
R6, R7, R8, R9: 1k; R0805
R10, R11: 220; R0805
RESET: TACT; TACT-TS-1289
SWITCH: A-5104SMALL; A-5104-SMALL
U1: USD-SOCKETUSD; USD-SOCKET-PP
U$1: MIIScoreBoard V1.2; MIICHRONO
U$3: GROUP; TC33X
U$4: FREQ; TC33X
U$5: ID; TC33X
U$7: SI4432
Y1: 12Mhz; HC49UP

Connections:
32KHZ: IC1.1 (32KHZ), R14.1
+3V3: 662K1.2 (VOUT), +LED-.2, C4.1, IC1.2 (VCC), IC2.4 (VCC1), IC2.6 (VCC2), IC2.18 (VCC/ANALOG), IC2.20 (ANALOG_REFERENCE), ISP.2, R3.1, R6.1, R13.1, R14.2, R15.2, R16.2, U1.4 (VCC), U$3.1 (A), U$4.1 (A), U$5.1 (A), U$7.+3V3
ANT: ANT.1, J$1.SIG (SIGNAL), U$7.ANT
ANT-SDN: IC2.24 (ANALOG_1), U$7.SDN
ANT-SELECT: IC2.23 (ANALOG_0), U$7.NSEL
BAT-IN: SWITCH.1 (O)
BAT-OUT: 662K1.3 (VIN), C1.1, SWITCH.3 (S)
FREQ: IC2.26 (ANALOG_3), R2.2, U$4.2 (S)
GND: 662K1.1 (VSS), +LED-.1, -BAT+.1 (2), C1.2, C2.2, C3.2, C4.2, CN1.GND, IC1.5 (NC), IC1.6 (NC1), IC1.7 (NC2), IC1.8 (NC3), IC1.9 (NC4), IC1.10 (NC5), IC1.11 (NC6), IC1.12 (NC7), IC1.13 (GND), IC2.3 (GND1), IC2.5 (GND2), IC2.21 (GND/ANALOG), ISP.6, LED.2, LED.4, LED.6, LED.14, LED.16, R1.1, R2.1, R4.1, R12.2, RESET.TOP-1, U1.6 (GND), U$7.GND, U$7.GND1
GND-ANT: J$1.GND@0 (GND), J$1.GND@1 (GND), J$1.GND@2 (GND), J$1.GND@3 (GND), U$7.GND-ANT
GROUP: IC2.25 (ANALOG_2), R1.2, U$3.2 (S)
ID: IC2.19 (ANALOG_6), R4.2, U$5.2 (S)
KEYBOARD: IC2.22 (ANALOG_7), JP1.3, R11.1, R12.1
LED-A: IC2.2 (DIGITAL_4), LED.1
LED-B: IC2.9 (DIGITAL_5(PWM)), LED.3
LED-C: IC2.10 (DIGITAL_6(PWM)), LED.5
LED-D: IC2.11 (DIGITAL_7), LED.7
LED-G1: LED.9
LED-G2: LED.11
LED-LT: IC2.30 (DIGITAL_0(RX)), LED.13
LED-OE: IC2.31 (DIGITAL_1(TX)), LED.8
LED-R1: IC2.12 (DIGITAL_8), LED.10
LED-R2: LED.12
LED-SK: IC2.13 (DIGITAL_9(PWM)), LED.15
MISO: IC2.16 (DIGITAL_12), ISP.1, U1.7 (DO), U$7.SDO
MOSI: IC2.15 (DIGITAL_11(PWM)), ISP.4, U1.3 (DI), U$7.SDI
unnamed: JP1.4, R9.2
unnamed: JP1.7, R6.2, R7.1
unnamed: JP1.6, R7.2, R8.1
unnamed: JP1.5, R8.2, R9.1
unnamed: JP1.1, R10.2
unnamed: C3.1, IC2.8 (CRYSTAL2), Y1.1
unnamed: C2.1, IC2.7 (CRYSTAL1), Y1.2
unnamed: JP1.2, R10.1, R11.2
unnamed: IC1.14 (VBAT), R17.2
NIRQ: IC2.1 (DIGITAL_3(PWM)), U$7.NIRQ
RESET: IC1.4 (/RST), IC2.29 (RESET), ISP.5, R3.2, RESET.BOT-2
SCK: IC2.17 (DIGITAL_13), ISP.3, U1.5 (SCK), U$7.SCLK
SCL: CN1.D+, IC1.16 (SCL), IC2.28 (ANALOG_5), R15.1
SD-SELECT: IC2.14 (DIGITAL_10(PWM)), U1.2 (CS)
SDA: CN1.D-, IC1.15 (SDA), IC2.27 (ANALOG_4), R16.1
SQW: IC1.3 (SQW/INT), R13.2
SW: CN1.ID, IC2.32 (DIGITAL_2)
VBAT: -BAT+.2 (1), CN1.VBUS, R17.1, SWITCH.2

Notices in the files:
parts and their libraries:
SparkFun: Licensing: CC v3.0 Share-Alike You are welcome to use this library for commercial purposes.
eagle-library-edeca: This is v1 and is licensed under the Creative Commons (Attribution-Non-Commercial-Share Alike 2.0 UK)
